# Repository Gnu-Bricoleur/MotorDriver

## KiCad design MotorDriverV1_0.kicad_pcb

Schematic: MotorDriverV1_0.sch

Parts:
C1: 1uF; CP_Radial_D5.0mm_P2.50mm
C2: 0.33uF; R_Axial_DIN0204_L3.6mm_D1.6mm_P5.08mm_Horizontal
C3: 1200uF; CP_Radial_D7.5mm_P2.50mm
C4: 0.1uF; R_Axial_DIN0204_L3.6mm_D1.6mm_P5.08mm_Horizontal
C5, C6, C7, C8: 10nF; R_Axial_DIN0204_L3.6mm_D1.6mm_P5.08mm_Horizontal
D1, D2, D3, D4: LED; LED_0603_1608Metric_Pad1.05x0.95mm_HandSolder
D5: LED; PinHeader_1x02_P2.54mm_Vertical
J1, J5, J6: Screw_Terminal_01x02; PhoenixContact_MSTBA_2,5_2-G_1x02_P5.00mm_Horizontal
J2, J3, J4: Conn_01x02; PinHeader_1x02_P2.54mm_Vertical
J7, J8, J9, J11, J12, J13: Conn_01x01; PinHeader_1x01_P2.54mm_Vertical
J10: Conn_02x06_Odd_Even; IDC-Header_2x06_P2.54mm_Vertical
P1: Power; Socket_Strip_Arduino_1x08
P2: Analog; Socket_Strip_Arduino_1x06
P3: Digital; Socket_Strip_Arduino_1x10
P4: Digital; Socket_Strip_Arduino_1x08
P5, P6, P7, P8: CONN_01X01; Arduino_1pin
R1, R3, R4: 1k; R_0603_1608Metric_Pad1.05x0.95mm_HandSolder
R2: 1K; R_0603_1608Metric_Pad1.05x0.95mm_HandSolder
R5, R6: 2.7k; R_Axial_DIN0207_L6.3mm_D2.5mm_P10.16mm_Horizontal
R7: 1k; R_Axial_DIN0207_L6.3mm_D2.5mm_P10.16mm_Horizontal
U1: LM324; SOIC-14_3.9x8.7mm_P1.27mm
U2: L7809; PinHeader_1x03_P2.54mm_Vertical
U3, U4: LMD18200; TO-220-11_P3.4x5.08mm_StaggerOdd_Lead4.85mm_Vertical

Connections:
+5V: P1.5, U1.4 (V+)
/2: J10.7, P4.6, U1.5 (+), U3.3
/3(**): J10.9, P4.5, U1.3 (+), U3.5
/4: J10.6, P4.4, U1.12 (+), U4.3
/5(**): J10.4, P4.3, U1.10 (+), U4.5
/6(**): J9.1, P4.2
/7: J7.1, P4.1
/8: J11.1, P3.10
/9(**): J13.1, P3.9
/A0: J8.1, P2.1
/A1: J12.1, P2.2
/BR1: J3.2, J10.5, U3.4
/BR2: J4.2, J10.8, U4.4
/CSEN1: J10.3, R5.1, U3.8
/CSEN2: J10.10, R6.1, U4.8
/TF1: J10.1, U3.9
/TF2: J10.12, U4.9
/Vin: C4.1, D5.2, P1.8, U2.3 (OUT)
/Vs: C1.1, C3.1, J1.2, J2.1, U3.6, U4.6
GND: C1.2, C2.2, C3.2, C4.2, J1.1, J3.1, J4.1, J10.2, J10.11, P1.6, P1.7, P3.4, R1.1, R2.1, R3.1, R4.1, R5.2, R6.2, R7.2, U1.11 (V-), U2.2 (GND), U3.7, U4.7
unnamed: C2.1, J2.2, U2.1 (IN)
unnamed: C5.1, J5.1, U3.2
unnamed: C5.2, U3.1
unnamed: C6.1, U3.11
unnamed: C6.2, J5.2, U3.10
unnamed: C7.1, J6.1, U4.2
unnamed: C7.2, U4.1
unnamed: C8.1, U4.11
unnamed: C8.2, J6.2, U4.10
unnamed: D1.1, R1.2
unnamed: D1.2, U1.1, U1.2 (-)
unnamed: D2.1, R2.2
unnamed: D2.2, U1.6 (-), U1.7
unnamed: D3.1, R3.2
unnamed: D3.2, U1.8, U1.9 (-)
unnamed: D4.1, R4.2
unnamed: D4.2, U1.13 (-), U1.14
unnamed: D5.1, R7.1

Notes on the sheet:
Holes
Shield for Arduino that uses the same pin disposition like "Uno" board Rev 3.
BR1 -- 6(**) CSEN1 -- A0 TF1 -- 7 BR2 -- 8 CSEN2 -- A1 TF2 -- 9(**) positionne de facon a mettre un jumper en configuration shield

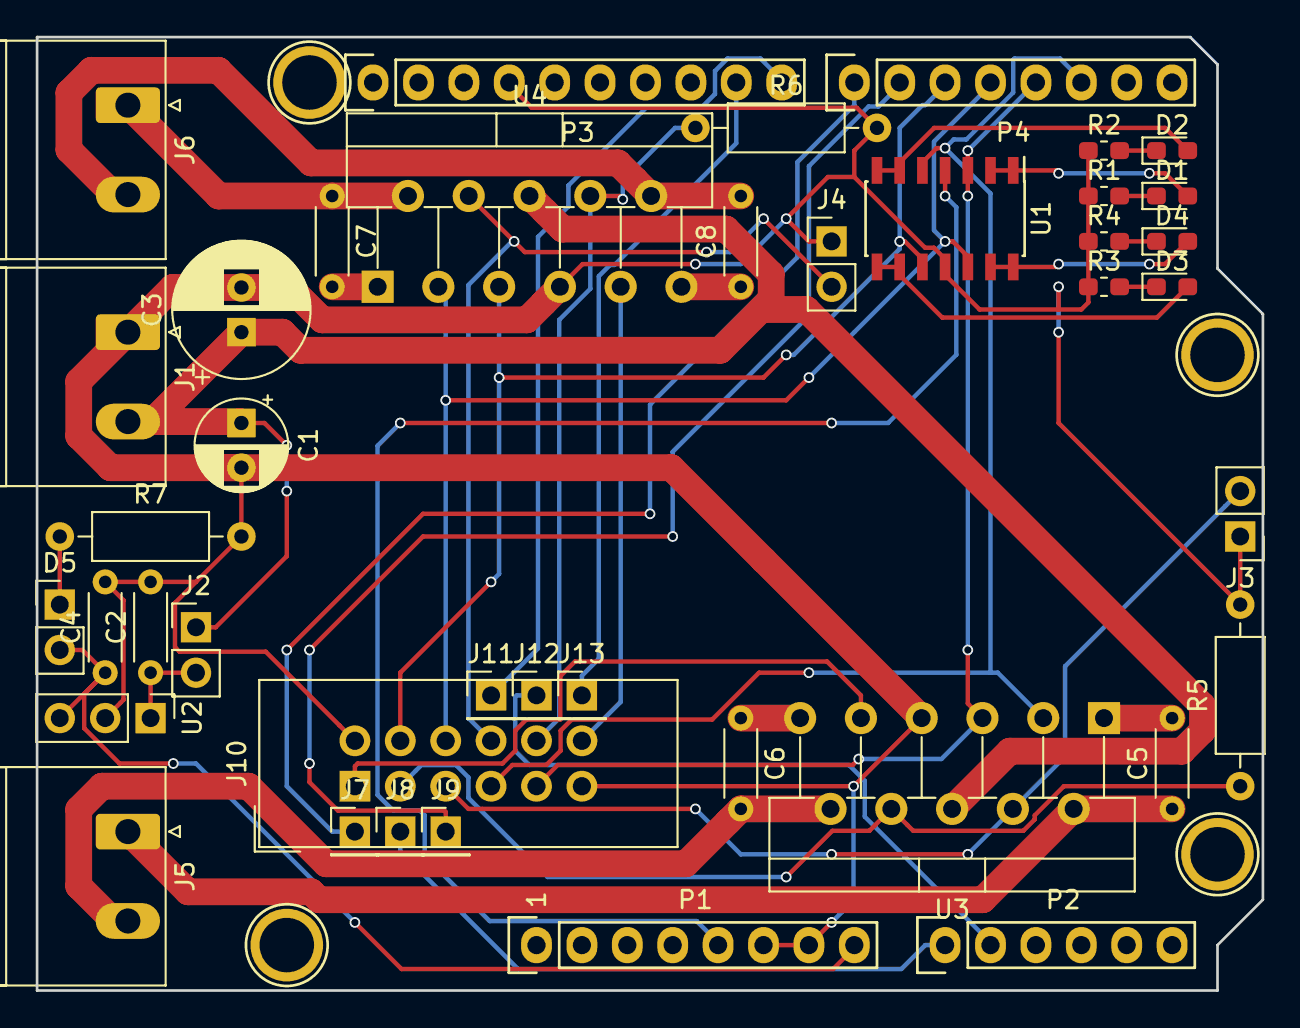
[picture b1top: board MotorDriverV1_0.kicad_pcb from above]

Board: 2 copper layers, 68.6 x 53.3 mm, 45 parts (0 on the bottom side), 38 nets.

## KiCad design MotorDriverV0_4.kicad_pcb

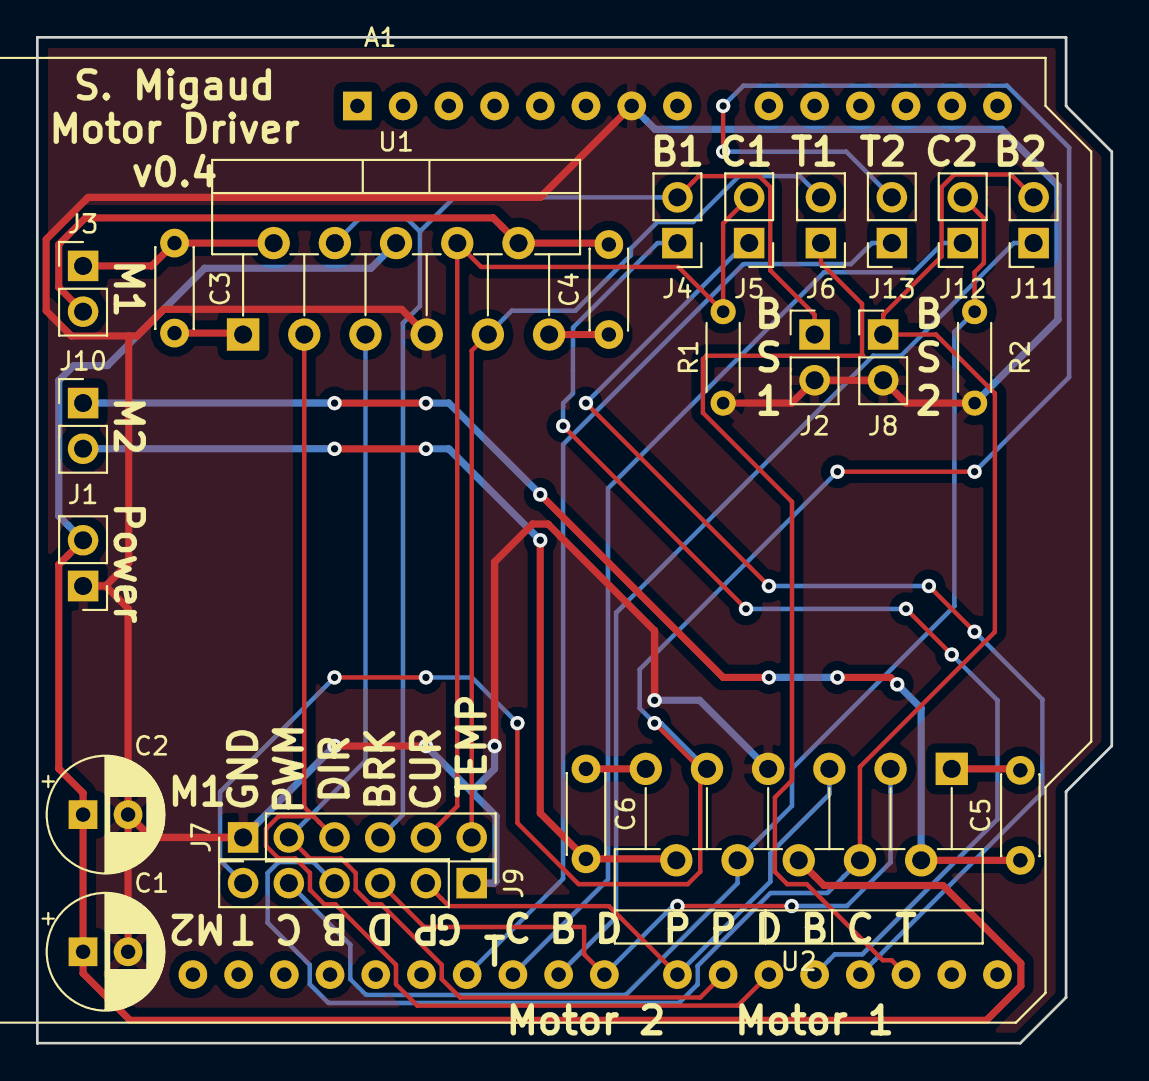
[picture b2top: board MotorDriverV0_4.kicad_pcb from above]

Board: 2 copper layers, 59.7 x 55.9 mm, 24 parts (0 on the bottom side), 26 nets.

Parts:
A1: Arduino_UNO_R3
C1: 1uF; CP_Radial_D6.3mm_P2.50mm
C2: 1200uF; CP_Radial_D6.3mm_P2.50mm
C3, C4, C5, C6: 10nF; C_Disc_D4.3mm_W1.9mm_P5.00mm
J1, J3, J10: Screw_Terminal_01x02; PinHeader_1x02_P2.54mm_Vertical
J2, J4, J5, J6, J8: Conn_01x02_Male; PinHeader_1x02_P2.54mm_Vertical
J7, J9: Conn_01x06_Male; PinHeader_1x06_P2.54mm_Vertical
J11, J12, J13: Conn_01x02_Male; PinSocket_1x02_P2.54mm_Vertical
R1, R2: 2.7k; R_Axial_DIN0204_L3.6mm_D1.6mm_P5.08mm_Horizontal
U1, U2: LMD18200; TO-220-11_P3.4x5.08mm_StaggerOdd_Lead4.85mm_Vertical

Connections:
BRK1: A1.19, J4.1
BRK2: A1.24, J11.1
CUR1: A1.18, J5.1
CUR2: A1.25, J12.1
DIR1: A1.20, J7.3, U1.3
DIR2: A1.23, J9.3, U2.3
GND: A1.7, C1.2, C2.2, J1.1, J2.2, J7.1, J8.2, J9.1, R1.1, R2.1, U1.7, U2.7
unnamed: C3.1, J3.1, U1.2
unnamed: C3.2, U1.1
unnamed: C4.1, U1.11
unnamed: C4.2, J3.2, U1.10
unnamed: C5.1, J10.1, U2.2
unnamed: C5.2, U2.1
unnamed: C6.1, U2.11
unnamed: C6.2, J10.2, U2.10
unnamed: J2.1, J4.2, J7.4, U1.4
unnamed: J5.2, J7.5, R1.2, U1.8
unnamed: J6.2, J7.6, U1.9
unnamed: J8.1, J9.4, J11.2, U2.4
unnamed: J9.5, J12.2, R2.2, U2.8
unnamed: J9.6, J13.2, U2.9
PWM1: A1.21, J7.2, U1.5
PWM2: A1.22, J9.2, U2.5
TEMP1: A1.17, J6.1
TEMP2: A1.26, J13.1
VS: C1.1, C2.1, J1.2, U1.6, U2.6

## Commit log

2018-11-15 fixing weird corruption problem
2018-11-15 updating gerber
2018-11-16 fixing again weird corruption problem
2019-01-28 V1.0
    iteration after receiveing the first PCBs
2019-02-01 some routing and compoment placement
2019-02-04 routing completed
2019-02-08 routing completerd
2019-02-08 routung finihed
2019-03-29 To JLCPCB
